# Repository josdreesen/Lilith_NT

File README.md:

# Lilith_NT

This database documents my attempt to recreate the 1980's ETH Lilith Modula-2 workstation. Both hardware and software is to be documented here.

The actual CPU will be identical to the original machine, shortcuts will be made to avoid some of the original problems :
- The disk was either a Honeywell-Bull 10Mb cartridge drive, or a 15Mb  MFM drive, controlled by a WD1001.
- NEW -> This is to be replaced by a DOM-disk with ATA interface.
- The original ha 4 PCB's with each 32 4116-type DRAM-chips, for a total of 128K 16bit words.
- NEW -> a single PCB will hold 16 256Kx4 chips, for a total of 1M 16bit words.
  Other characteristics will remain the same ( i.e. write access in 16bit words, read access in either 16bit of 64bit words)
- NEW : DIN41642 connectors will replace the original, hard to find and expensive 1.125" spaced board edge connectors.

Lilith-NT's hardware consists of 8 PCB's, all newly designed in a more compact format (Dual eurocard, 233.4mm x 152mm)

DPU : a MC6802 based debugging aid. This takes over the main busses in the system, allowing direct access to the hardware.
      Original schematic, slightly newer memory chips, new board layout.
      Not needed in normal operation of a Lilith.

ALU : the actual CPU, consisting of 4 AMD2901 bitslices, hardware stack and a 16bit barrel shifter.
      Original schematic with a new board layout.

MCU : microcode unit. Contains the microprogram that controls the bitslices, also has the microcode sequencer and clockgen circuitry.
      Original schematic with a new PCB layout, but now also has the memory address registers, originally in the CDP board.

IFU : instruction fetch unit. Also contains boot eprom. Original schematic with a new board layout.

DRAM: main memory, consisting of 16 4x256K DRAMs. Updated design of the original, using much denser chips. 
      Also contains the Dataregister which was originally in the CDP board.
      
DSP : Display unit / Videocard. Original schematic with a new board layout.      

IOP : IO board : new design, new PCB combining PS2 keyboard & mouse interface. 
      Also contains 2 serial channels, ATA/DOM disk, floppy interface and RTC chip.
      
Mainboard : carrries the above mentioned boards in dedicated slots.
            New design, using DIN-connectors instead of the PCB cardedge connectors to reduce cost and increase reliability.
            Goldplating PCB's is considerable more expensive than just using the DIN connectors.

The subdirectories, one for each pcb,  contain a .zip file with the gerbers, a .pdf with the schematic, a rendering of the PCB
and the Kicad Database itself.

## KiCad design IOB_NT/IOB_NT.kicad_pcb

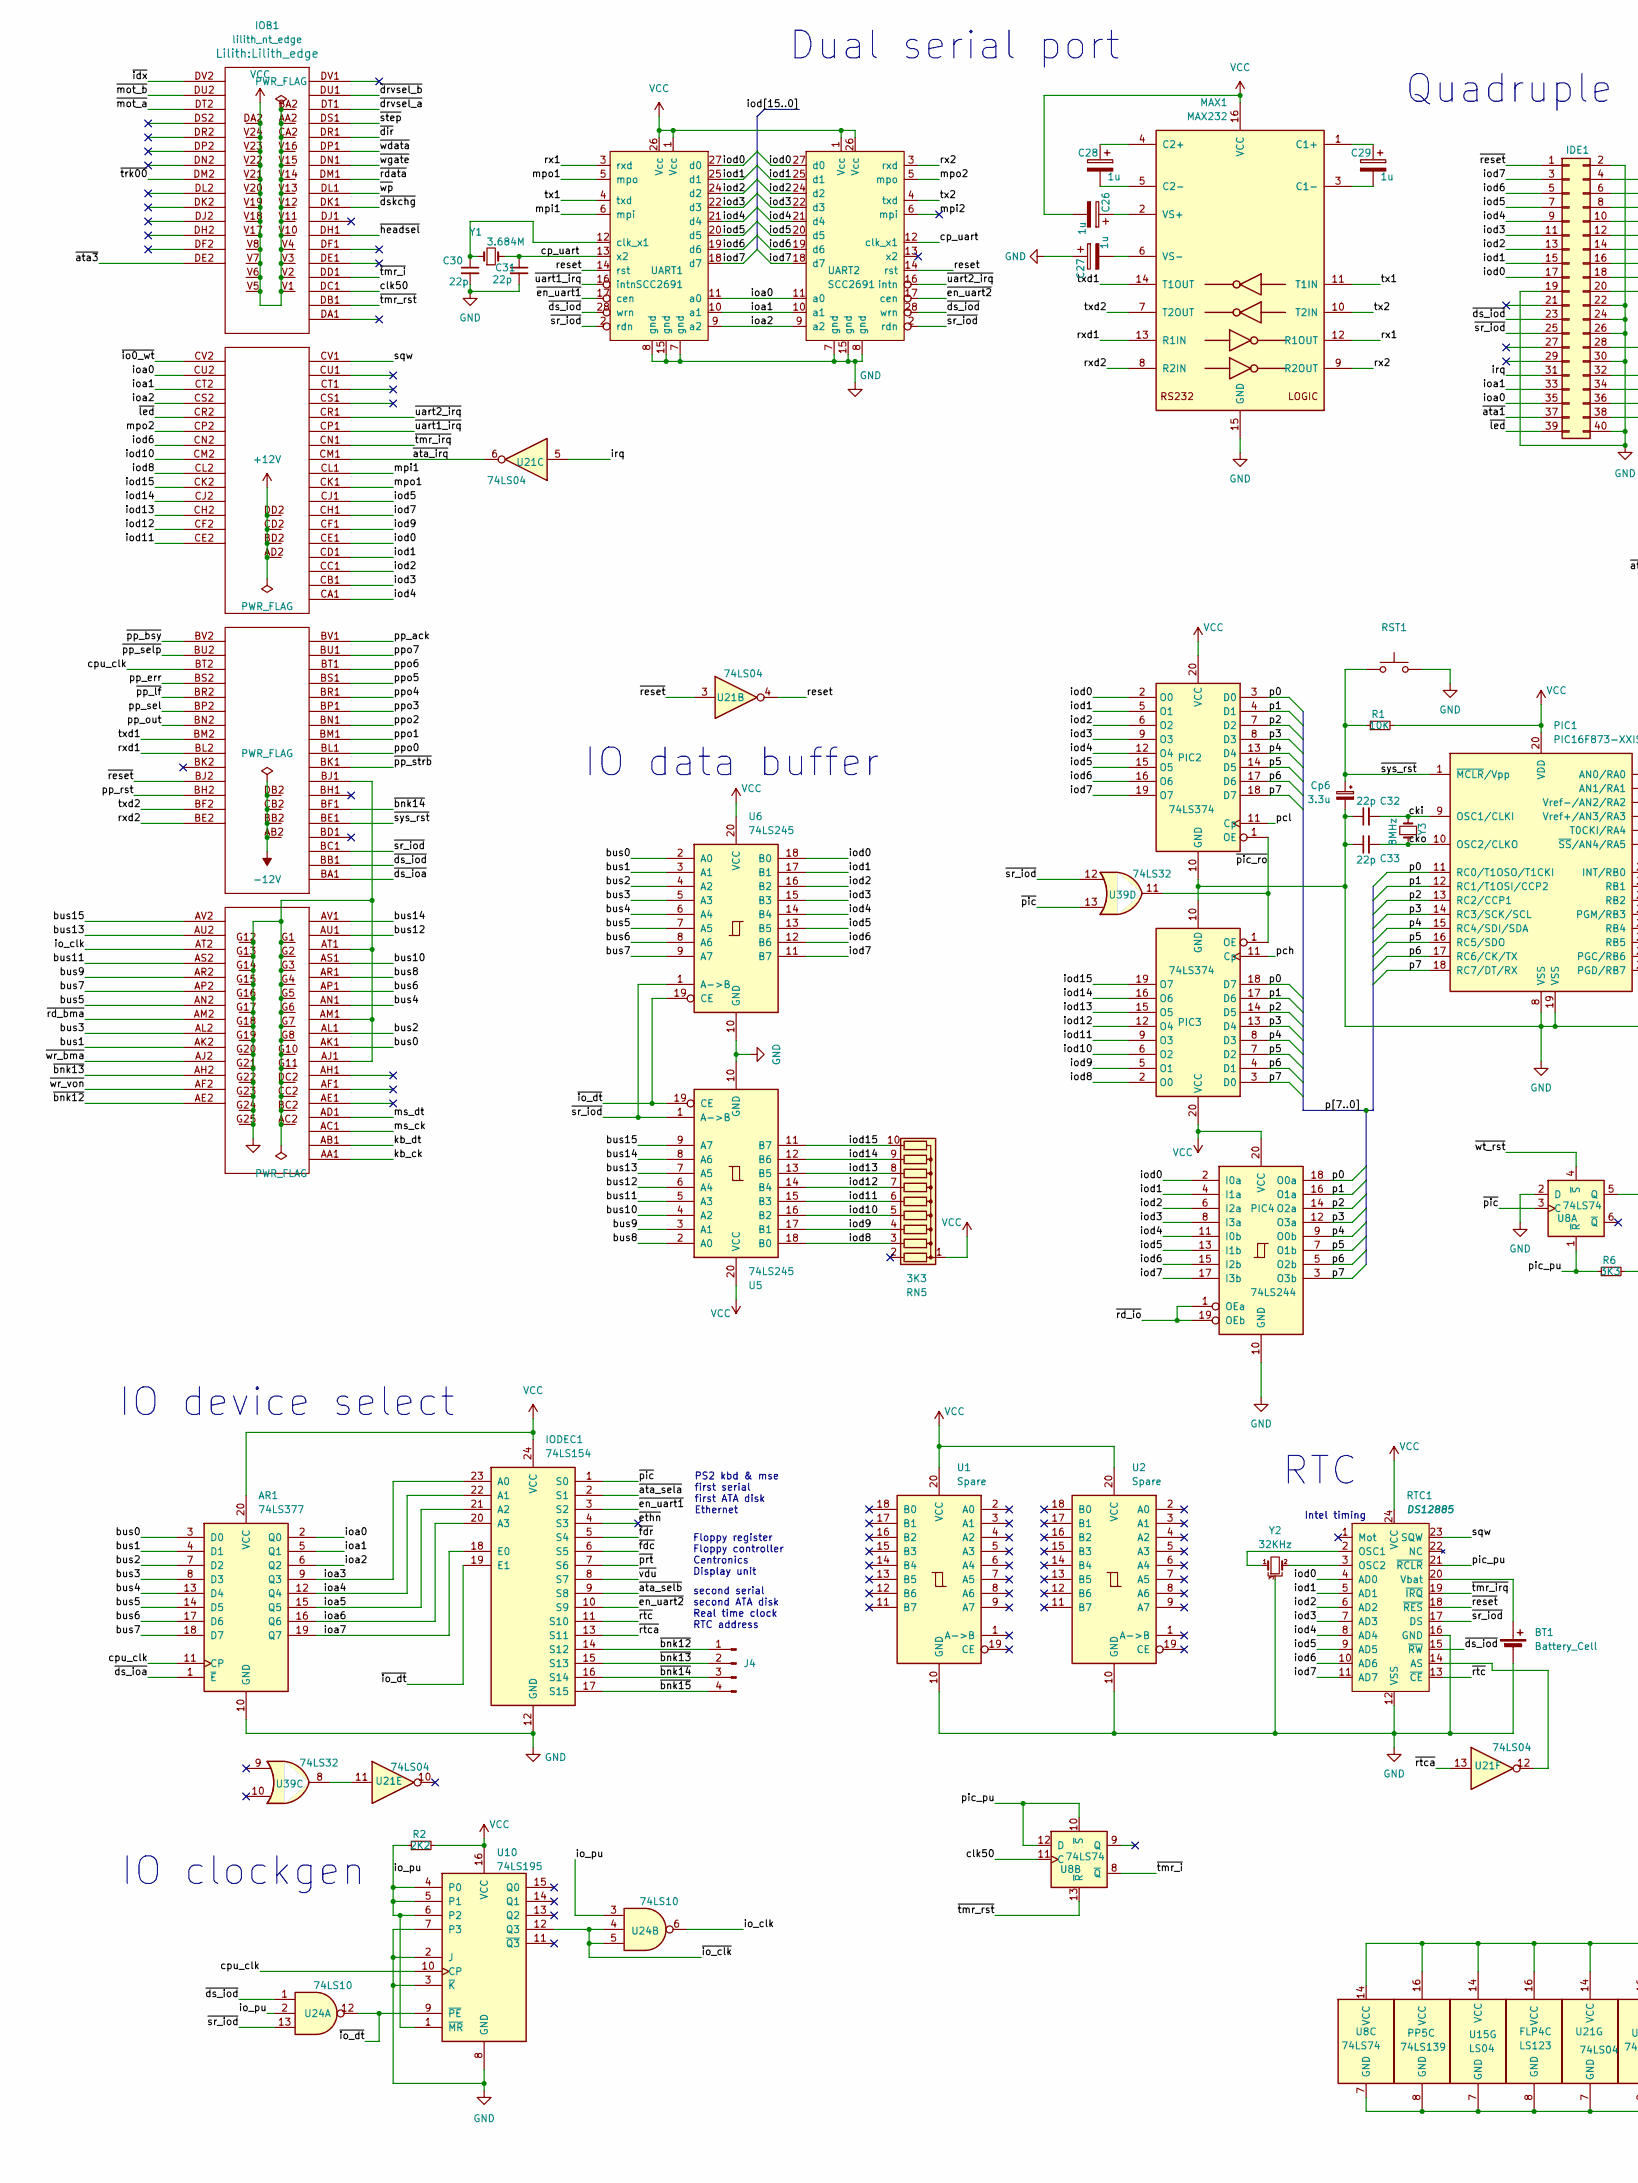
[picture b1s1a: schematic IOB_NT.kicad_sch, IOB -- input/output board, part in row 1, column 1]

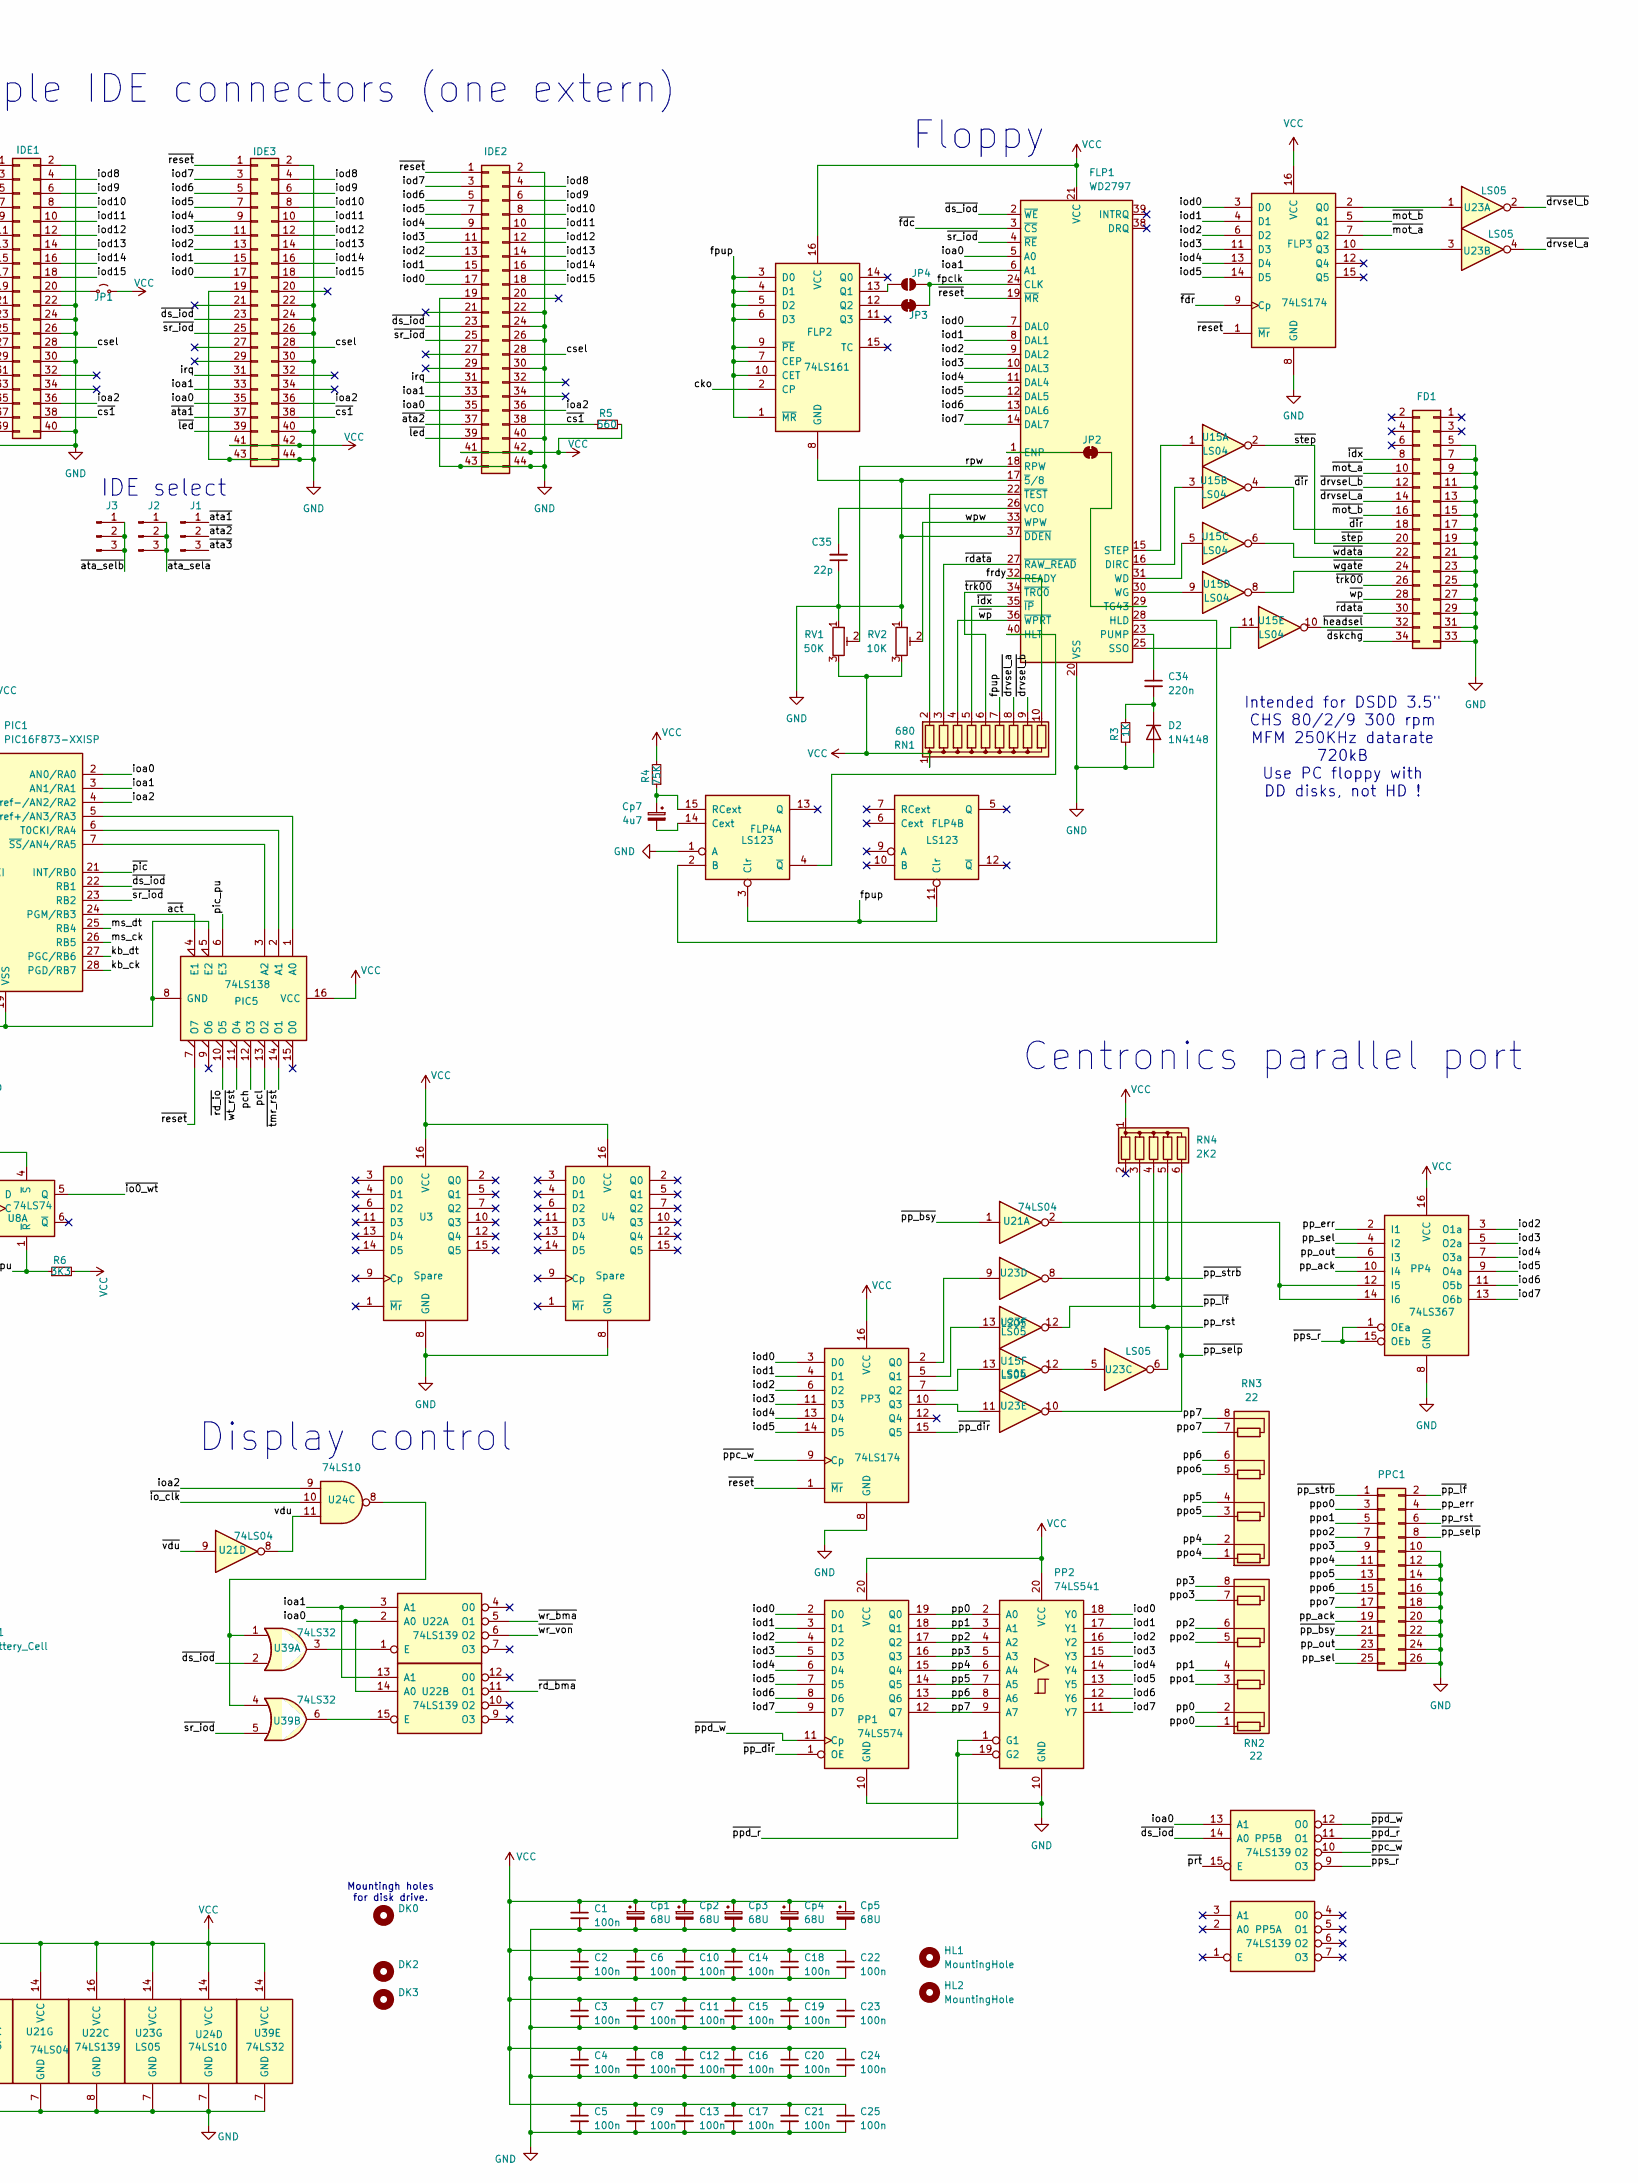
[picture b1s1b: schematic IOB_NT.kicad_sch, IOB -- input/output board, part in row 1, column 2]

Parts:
AR1: 74LS377; DIP-20_W7.62mm
BT1: Battery_Cell; BatteryHolder_MYOUNG_BS-07-A1BJ001_CR2032
C1, C2, C3, C4, C5, C6, C7, C8, C9, C10, C11, C12, C13, C14, C15, C16, C17, C18, C19, C20, C21, C22, C23, C24, C25: 100n; C_1206_3216Metric_Pad1.33x1.80mm_HandSolder
C26, C27, C28, C29: 1u; CP_Radial_Tantal_D4.5mm_P2.50mm
C30, C31: 22p; C_0805_2012Metric_Pad1.18x1.45mm_HandSolder
C32, C33: 22p; C_0805_2012Metric
C34: 220n; C_Rect_L7.0mm_W2.5mm_P5.00mm
C35: 22p; C_Disc_D3.0mm_W2.0mm_P2.50mm
Cp1, Cp2, Cp3, Cp4, Cp5: 68U; CP_PHP
Cp6: 3.3u; CP_Radial_D5.0mm_P2.50mm
Cp7: 4u7; CP_Radial_Tantal_D4.5mm_P2.50mm
D2: 1N4148; D_DO-35_SOD27_P7.62mm_Horizontal
DK0, DK2, DK3: MountingHole; MountingHole_2.7mm_M2.5
FD1: Conn_02x17_Odd_Even; IDC-Header_2x17_P2.54mm_Vertical
FLP1: WD2797; DIP-40_W15.24mm
FLP2: 74LS161; DIP-16_W7.62mm
FLP3: 74LS174; DIP-16_W7.62mm
FLP4: LS123; DIP-16_W7.62mm
HL1, HL2: MountingHole; Handle
IDE1: Conn_02x20_Odd_Even; IDC-Header_2x20_P2.54mm_Horizontal
IDE2, IDE3: Conn_02x22_Odd_Even; PinHeader_2x22_P2.00mm_Vertical
IOB1: lilith_nt_edge; Lilith_edge
IODEC1: 74LS154; DIP-24_W15.24mm
J1, J2, J3: Conn_01x03_Pin; PinHeader_1x03_P2.54mm_Vertical
J4: Conn_01x04_Pin; PinHeader_1x04_P2.54mm_Vertical
JP1: Jumper_2_Small_Open; PinHeader_1x02_P2.54mm_Vertical
JP2, JP3: SolderJumper_2_Bridged; SolderJumper-2_P1.3mm_Bridged_RoundedPad1.0x1.5mm
JP4: SolderJumper_2_Open; SolderJumper-2_P1.3mm_Open_RoundedPad1.0x1.5mm
MAX1: MAX232; DIP-16_W7.62mm
PIC1: PIC16F873-XXISP; DIP-28_W7.62mm_Socket
PIC2, PIC3: 74LS374; DIP-20_W7.62mm
PIC4: 74LS244; DIP-20_W7.62mm
PIC5: 74LS138; DIP-16_W7.62mm
PP1: 74LS574; DIP-20_W7.62mm
PP2: 74LS541; DIP-20_W7.62mm
PP3: 74LS174; DIP-16_W7.62mm
PP4: 74LS367; DIP-16_W7.62mm
PP5: 74LS139; DIP-16_W7.62mm
PPC1: Conn_02x13_Odd_Even; IDC-Header_2x13_P2.54mm_Vertical
R1: 10K; R_Axial_DIN0204_L3.6mm_D1.6mm_P7.62mm_Horizontal
R2: 2K2; R_Axial_DIN0204_L3.6mm_D1.6mm_P7.62mm_Horizontal
R3: 1K; R_Axial_DIN0204_L3.6mm_D1.6mm_P7.62mm_Horizontal
R4: 75K; R_Axial_DIN0204_L3.6mm_D1.6mm_P7.62mm_Horizontal
R5: 560; R_Axial_DIN0204_L3.6mm_D1.6mm_P7.62mm_Horizontal
R6: 3K3; R_Axial_DIN0204_L3.6mm_D1.6mm_P7.62mm_Horizontal
RN1: 680; R_Array_SIP10
RN2, RN3: 22; R_Array_SIP8
RN4: 2K2; R_Array_SIP6
RN5: 3K3; R_Array_SIP10
RST1: SW_Push; SW_PUSH_6mm
RTC1: DS12885; DIP-24_W15.24mm
RV1: 50K; Potentiometer_Bourns_3006P_Horizontal
RV2: 10K; Potentiometer_Bourns_3006P_Horizontal
U1, U2: Spare; DIP-20_W7.62mm
U3, U4: Spare; DIP-16_W7.62mm
U5, U6: 74LS245; DIP-20_W7.62mm
U8: 74LS74; DIP-14_W7.62mm
U10: 74LS195; DIP-16_W7.62mm
U15: LS04; DIP-14_W7.62mm
U21: 74LS04; DIP-14_W7.62mm
U22: 74LS139; DIP-16_W7.62mm
U23: LS05; DIP-14_W7.62mm
U24: 74LS10; DIP-14_W7.62mm
U39: 74LS32; DIP-14_W7.62mm
UART1, UART2: SCC2691; PLCC-28_THT-Socket
Y1: 3.684M; Crystal_HC49-U_Vertical
Y2: 32KHz; Crystal_AT310_D3.0mm_L10.0mm_Horizontal_1EP_style2
Y3: 8MHz; Crystal_HC52-6mm_Vertical

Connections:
+12V: IOB1.AD2, IOB1.BD2, IOB1.CD2, IOB1.DD2
-12V: IOB1.AB2, IOB1.BB2, IOB1.CB2, IOB1.DB2
/bus0: AR1.3 (D0), IOB1.AK1, U6.2 (A0)
/bus1: AR1.4 (D1), IOB1.AK2, U6.3 (A1)
/bus2: AR1.7 (D2), IOB1.AL1, U6.4 (A2)
/bus3: AR1.8 (D3), IOB1.AL2, U6.5 (A3)
/bus4: AR1.13 (D4), IOB1.AN1, U6.6 (A4)
/bus5: AR1.14 (D5), IOB1.AN2, U6.7 (A5)
/bus6: AR1.17 (D6), IOB1.AP1, U6.8 (A6)
/bus7: AR1.18 (D7), IOB1.AP2, U6.9 (A7)
/bus8: IOB1.AR1, U5.2 (A0)
/bus9: IOB1.AR2, U5.3 (A1)
/bus10: IOB1.AS1, U5.4 (A2)
/bus11: IOB1.AS2, U5.5 (A3)
/bus12: IOB1.AU1, U5.6 (A4)
/bus13: IOB1.AU2, U5.7 (A5)
/bus14: IOB1.AV1, U5.8 (A6)
/bus15: IOB1.AV2, U5.9 (A7)
/cki: C32.2, PIC1.9 (OSC1/CLKI), Y3.2
/cko: C33.2, FLP2.2 (CP), PIC1.10 (OSC2/CLKO), Y3.1
/clk50: IOB1.DC1, U8.11 (C)
/cp_uart: C31.1, UART1.13 (x2), UART2.12 (clk_x1), Y1.2
/cpu_clk: AR1.11 (CP), IOB1.BT2, U10.10 (CP)
/csel: IDE1.28, IDE2.28, IDE3.28
/fpclk: FLP1.24 (CLK), JP3.2 (B), JP4.2 (B)
/fpup: FLP2.1 (~MR), FLP2.3 (D0), FLP2.4 (D1), FLP2.5 (D2), FLP2.6 (D3), FLP2.7 (CEP), FLP2.9 (~PE), FLP2.10 (CET), FLP4.3 (Clr), FLP4.11 (Clr), RN1.7 (R6)
/frdy: FLP1.32 (READY), RN1.10 (R9)
/io_clk: IOB1.AT2, U24.6
/io_pu: R2.1, U10.1 (~MR), U10.4 (P0), U10.5 (P1), U10.6 (P2), U24.2, U24.3
/ioa0: AR1.2 (Q0), FLP1.5 (A0), IDE1.35, IDE2.35, IDE3.35, IOB1.CU2, PIC1.2 (AN0/RA0), PP5.13 (A1), U22.2 (A0), U22.14 (A0), UART1.11 (a0), UART2.11 (a0)
/ioa1: AR1.5 (Q1), FLP1.6 (A1), IDE1.33, IDE2.33, IDE3.33, IOB1.CT2, PIC1.3 (AN1/RA1), U22.3 (A1), U22.13 (A1), UART1.10 (a1), UART2.10 (a1)
/ioa2: AR1.6 (Q2), IDE1.36, IDE2.36, IDE3.36, IOB1.CS2, PIC1.4 (Vref-/AN2/RA2), U24.9, UART1.9 (a2), UART2.9 (a2)
/ioa3: AR1.9 (Q3), IODEC1.23 (A0)
/ioa4: AR1.12 (Q4), IODEC1.22 (A1)
/ioa5: AR1.15 (Q5), IODEC1.21 (A2)
/ioa6: AR1.16 (Q6), IODEC1.20 (A3)
/ioa7: AR1.19 (Q7), IODEC1.18 (E0)
/iod0: FLP1.7 (DAL0), FLP3.3 (D0), IDE1.17, IDE2.17, IDE3.17, IOB1.CE1, PIC2.2 (O0), PIC4.2 (I0a), PP1.2 (D0), PP2.18 (Y0), PP3.3 (D0), RTC1.4 (AD0), U6.18 (B0), UART1.27 (d0), UART2.27 (d0)
/iod1: FLP1.8 (DAL1), FLP3.4 (D1), IDE1.15, IDE2.15, IDE3.15, IOB1.CD1, PIC2.5 (O1), PIC4.4 (I1a), PP1.3 (D1), PP2.17 (Y1), PP3.4 (D1), RTC1.5 (AD1), U6.17 (B1), UART1.25 (d1), UART2.25 (d1)
/iod2: FLP1.9 (DAL2), FLP3.6 (D2), IDE1.13, IDE2.13, IDE3.13, IOB1.CC1, PIC2.6 (O2), PIC4.6 (I2a), PP1.4 (D2), PP2.16 (Y2), PP3.6 (D2), PP4.3 (O1a), RTC1.6 (AD2), U6.16 (B2), UART1.24 (d2), UART2.24 (d2)
/iod3: FLP1.10 (DAL3), FLP3.11 (D3), IDE1.11, IDE2.11, IDE3.11, IOB1.CB1, PIC2.9 (O3), PIC4.8 (I3a), PP1.5 (D3), PP2.15 (Y3), PP3.11 (D3), PP4.5 (O2a), RTC1.7 (AD3), U6.15 (B3), UART1.22 (d3), UART2.22 (d3)
/iod4: FLP1.11 (DAL4), FLP3.13 (D4), IDE1.9, IDE2.9, IDE3.9, IOB1.CA1, PIC2.12 (O4), PIC4.11 (I0b), PP1.6 (D4), PP2.14 (Y4), PP3.13 (D4), PP4.7 (O3a), RTC1.8 (AD4), U6.14 (B4), UART1.21 (d4), UART2.21 (d4)
/iod5: FLP1.12 (DAL5), FLP3.14 (D5), IDE1.7, IDE2.7, IDE3.7, IOB1.CJ1, PIC2.15 (O5), PIC4.13 (I1b), PP1.7 (D5), PP2.13 (Y5), PP3.14 (D5), PP4.9 (O4a), RTC1.9 (AD5), U6.13 (B5), UART1.20 (d5), UART2.20 (d5)
/iod6: FLP1.13 (DAL6), IDE1.5, IDE2.5, IDE3.5, IOB1.CN2, PIC2.16 (O6), PIC4.15 (I2b), PP1.8 (D6), PP2.12 (Y6), PP4.11 (O5b), RTC1.10 (AD6), U6.12 (B6), UART1.19 (d6), UART2.19 (d6)
/iod7: FLP1.14 (DAL7), IDE1.3, IDE2.3, IDE3.3, IOB1.CH1, PIC2.19 (O7), PIC4.17 (I3b), PP1.9 (D7), PP2.11 (Y7), PP4.13 (O6b), RTC1.11 (AD7), U6.11 (B7), UART1.18 (d7), UART2.18 (d7)
/iod8: IDE1.4, IDE2.4, IDE3.4, IOB1.CL2, PIC3.2 (O0), RN5.3 (R2), U5.18 (B0)
/iod9: IDE1.6, IDE2.6, IDE3.6, IOB1.CF1, PIC3.5 (O1), RN5.4 (R3), U5.17 (B1)
/iod10: IDE1.8, IDE2.8, IDE3.8, IOB1.CM2, PIC3.6 (O2), RN5.5 (R4), U5.16 (B2)
/iod11: IDE1.10, IDE2.10, IDE3.10, IOB1.CE2, PIC3.9 (O3), RN5.6 (R5), U5.15 (B3)
/iod12: IDE1.12, IDE2.12, IDE3.12, IOB1.CF2, PIC3.12 (O4), RN5.7 (R6), U5.14 (B4)
/iod13: IDE1.14, IDE2.14, IDE3.14, IOB1.CH2, PIC3.15 (O5), RN5.8 (R7), U5.13 (B5)
/iod14: IDE1.16, IDE2.16, IDE3.16, IOB1.CJ2, PIC3.16 (O6), RN5.9 (R8), U5.12 (B6)
/iod15: IDE1.18, IDE2.18, IDE3.18, IOB1.CK2, PIC3.19 (O7), RN5.10 (R9), U5.11 (B7)
/irq: IDE1.31, IDE2.31, IDE3.31, U21.5
/kb_ck: IOB1.AA1, PIC1.28 (PGD/RB7)
/kb_dt: IOB1.AB1, PIC1.27 (PGC/RB6)
/mpi1: IOB1.CL1, UART1.6 (mpi)
/mpi2: UART2.6 (mpi)
/mpo1: IOB1.CK1, UART1.5 (mpo)
/mpo2: IOB1.CP2, UART2.5 (mpo)
/ms_ck: IOB1.AC1, PIC1.26 (RB5)
/ms_dt: IOB1.AD1, PIC1.25 (RB4)
/p0: PIC1.11 (RC0/T1OSO/T1CKI), PIC2.3 (D0), PIC3.18 (D7), PIC4.18 (O0a)
/p1: PIC1.12 (RC1/T1OSI/CCP2), PIC2.4 (D1), PIC3.17 (D6), PIC4.16 (O1a)
/p2: PIC1.13 (RC2/CCP1), PIC2.7 (D2), PIC3.14 (D5), PIC4.14 (O2a)
/p3: PIC1.14 (RC3/SCK/SCL), PIC2.8 (D3), PIC3.13 (D4), PIC4.12 (O3a)
/p4: PIC1.15 (RC4/SDI/SDA), PIC2.13 (D4), PIC3.8 (D3), PIC4.9 (O0b)
/p5: PIC1.16 (RC5/SDO), PIC2.14 (D5), PIC3.7 (D2), PIC4.7 (O1b)
/p6: PIC1.17 (RC6/CK/TX), PIC2.17 (D6), PIC3.4 (D1), PIC4.5 (O2b)
/p7: PIC1.18 (RC7/DT/RX), PIC2.18 (D7), PIC3.3 (D0), PIC4.3 (O3b)
/pch: PIC3.11 (Cp), PIC5.12 (O3)
/pcl: PIC2.11 (Cp), PIC5.13 (O2)
/pic_pu: PIC5.6 (E3), R6.1, RTC1.21 (~RCLR), U8.1 (~R), U8.10 (~S), U8.12 (D)
/pp0: PP1.19 (Q0), PP2.2 (A0), RN2.2 (R1.2)
/pp1: PP1.18 (Q1), PP2.3 (A1), RN2.4 (R2.2)
/pp2: PP1.17 (Q2), PP2.4 (A2), RN2.6 (R3.2)
/pp3: PP1.16 (Q3), PP2.5 (A3), RN2.8 (R4.2)
/pp4: PP1.15 (Q4), PP2.6 (A4), RN3.2 (R1.2)
/pp5: PP1.14 (Q5), PP2.7 (A5), RN3.4 (R2.2)
/pp6: PP1.13 (Q6), PP2.8 (A6), RN3.6 (R3.2)
/pp7: PP1.12 (Q7), PP2.9 (A7), RN3.8 (R4.2)
/pp_ack: IOB1.BV1, PP4.10 (I4), PPC1.19
/pp_err: IOB1.BS2, PP4.2 (I1), PPC1.4
/pp_out: IOB1.BN2, PP4.6 (I3), PPC1.23
/pp_rst: IOB1.BH2, PPC1.6, RN4.3 (R2), U23.6
/pp_sel: IOB1.BP2, PP4.4 (I2), PPC1.25
/ppo0: IOB1.BL1, PPC1.3, RN2.1 (R1.1)
/ppo1: IOB1.BM1, PPC1.5, RN2.3 (R2.1)
/ppo2: IOB1.BN1, PPC1.7, RN2.5 (R3.1)
/ppo3: IOB1.BP1, PPC1.9, RN2.7 (R4.1)
/ppo4: IOB1.BR1, PPC1.11, RN3.1 (R1.1)
/ppo5: IOB1.BS1, PPC1.13, RN3.3 (R2.1)
/ppo6: IOB1.BT1, PPC1.15, RN3.5 (R3.1)
/ppo7: IOB1.BU1, PPC1.17, RN3.7 (R4.1)
/reset: U21.4, UART1.14 (rst), UART2.14 (rst)
/rpw: FLP1.18 (RPW), RV1.2
/rx1: MAX1.12 (R1OUT), UART1.3 (rxd)
/rx2: MAX1.9 (R2OUT), UART2.3 (rxd)
/rxd1: IOB1.BL2, MAX1.13 (R1IN)
/rxd2: IOB1.BE2, MAX1.8 (R2IN)
/sqw: IOB1.CV1, RTC1.23 (SQW)
/tx1: MAX1.11 (T1IN), UART1.4 (txd)
/tx2: MAX1.10 (T2IN), UART2.4 (txd)
/txd1: IOB1.BM2, MAX1.14 (T1OUT)
/txd2: IOB1.BF2, MAX1.7 (T2OUT)
/vdu: U21.8, U24.11
/wpw: FLP1.33 (WPW), RV2.2
/~act: PIC1.24 (PGM/RB3), PIC5.4 (E1)
/~ata1: IDE1.37, IDE3.37, J1.1
/~ata2: IDE2.37, J1.2
/~ata3: IOB1.DE2, J1.3
/~ata_irq: IOB1.CM1, U21.6
/~ata_sela: IODEC1.2 (S1), J2.1, J2.2, J2.3
/~ata_selb: IODEC1.9 (S8), J3.1, J3.2, J3.3
/~bnk12: IOB1.AE2, IODEC1.14 (S12), J4.1
/~bnk13: IOB1.AH2, IODEC1.15 (S13), J4.2
/~bnk14: IOB1.BF1, IODEC1.16 (S14), J4.3
/~bnk15: IODEC1.17 (S15), J4.4
/~cs1: IDE1.38, IDE2.38, IDE3.38, R5.1
/~dir: FD1.18, IOB1.DR1, U15.4
/~drvsel_a: FD1.14, IOB1.DT1, RN1.8 (R7), U23.4
/~drvsel_b: FD1.12, IOB1.DU1, RN1.9 (R8), U23.2
/~ds_ioa: AR1.1 (~E), IOB1.BA1
/~ds_iod: FLP1.2 (~WE), IDE1.23, IDE2.23, IDE3.23, IOB1.BB1, PIC1.22 (RB1), PP5.14 (A0), RTC1.15 (~RW), U24.1, U39.2, UART1.28 (wrn), UART2.28 (wrn)
/~dskchg: FD1.34, IOB1.DK1
/~en_uart1: IODEC1.3 (S2), UART1.17 (cen)
/~en_uart2: IODEC1.10 (S9), UART2.17 (cen)
/~ethn: IODEC1.4 (S3)
/~fdc: FLP1.3 (~CS), IODEC1.6 (S5)
/~fdr: FLP3.9 (Cp), IODEC1.5 (S4)
/~headsel: FD1.32, IOB1.DH1, U15.10
/~idx: FD1.8, FLP1.35 (~IP), IOB1.DV2, RN1.5 (R4)
/~io0_wt: IOB1.CV2, U8.5 (Q)
/~io_clk: U10.12 (Q3), U24.4, U24.5, U24.10
/~io_dt: IODEC1.19 (E1), U5.19 (CE), U6.19 (CE), U10.9 (~PE), U24.12
/~led: IDE1.39, IDE2.39, IDE3.39, IOB1.CR2
/~mot_a: FD1.10, FLP3.7 (Q2), IOB1.DT2
/~mot_b: FD1.16, FLP3.5 (Q1), IOB1.DU2
/~pic_ro: PIC2.1 (OE), PIC3.1 (OE), U39.11
/~pic: IODEC1.1 (S0), PIC1.21 (INT/RB0), U8.3 (C), U39.13
/~pp_bsy: IOB1.BV2, PPC1.21, U21.1
/~pp_dir: PP1.1 (OE), PP3.15 (Q5)
/~pp_lf: IOB1.BR2, PPC1.2, RN4.4 (R3), U23.12
/~pp_selp: IOB1.BU2, PPC1.8, RN4.6 (R5), U23.10
/~pp_strb: IOB1.BK1, PPC1.1, RN4.5 (R4), U23.8
/~ppc_w: PP3.9 (Cp), PP5.10 (O2)
/~ppd_r: PP2.1 (G1), PP2.19 (G2), PP5.11 (O1)
/~ppd_w: PP1.11 (Cp), PP5.12 (O0)
/~pps_r: PP4.1 (OEa), PP4.15 (OEb), PP5.9 (O3)
/~prt: IODEC1.7 (S6), PP5.15 (E)
/~rd_bma: IOB1.AM2, U22.11 (O1)
/~rd_io: PIC4.1 (OEa), PIC4.19 (OEb), PIC5.10 (O5)
/~rdata: FD1.30, FLP1.27 (~RAW_READ), IOB1.DM1, RN1.3 (R2)
/~reset: FLP1.19 (~MR), FLP3.1 (~Mr), IDE1.1, IDE2.1, IDE3.1, IOB1.BJ2, PIC5.7 (O7), PP3.1 (~Mr), RTC1.18 (~RES), U21.3
/~rtca: IODEC1.13 (S11), U21.13
/~rtc: IODEC1.11 (S10), RTC1.13 (~CE)
/~sr_iod: FLP1.4 (~RE), IDE1.25, IDE2.25, IDE3.25, IOB1.BC1, PIC1.23 (RB2), RTC1.17 (DS), U5.1 (A->B), U6.1 (A->B), U24.13, U39.5, U39.12, UART1.2 (rdn), UART2.2 (rdn)
/~step: FD1.20, IOB1.DS1, U15.2
/~sys_rst: Cp6.1, IOB1.BE1, PIC1.1 (~MCLR/Vpp), R1.1, RST1.1
/~tmr_irq: IOB1.CN1, RTC1.19 (~IRQ)
/~tmr_i: IOB1.DD1, U8.8 (~Q)
/~tmr_rst: IOB1.DB1, PIC5.14 (O1), U8.13 (~R)
/~trk00: FD1.26, FLP1.34 (~TR00), IOB1.DM2, RN1.6 (R5)
/~uart1_irq: IOB1.CP1, UART1.16 (intn)
/~uart2_irq: IOB1.CR1, UART2.16 (intn)
/~vdu: IODEC1.8 (S7), U21.9
/~wdata: FD1.22, IOB1.DP1, U15.6
/~wgate: FD1.24, IOB1.DN1, U15.8
/~wp: FD1.28, FLP1.36 (~WPRT), IOB1.DL1, RN1.4 (R3)
/~wr_bma: IOB1.AJ2, U22.5 (O1)
/~wr_von: IOB1.AF2, U22.6 (O2)
/~wt_rst: PIC5.11 (O4), U8.4 (~S)
GND: AR1.10 (GND), BT1.2 (-), C1.2, C2.2, C3.2, C4.2, C5.2, C6.2, C7.2, C8.2, C9.2, C10.2, C11.2, C12.2, C13.2, C14.2, C15.2, C16.2, C17.2, C18.2, C19.2, C20.2, C21.2, C22.2, C23.2, C24.2, C25.2, C27.1, C30.2, C31.2, C32.1, C33.1, C35.1, Cp1.2, Cp2.2, Cp3.2, Cp4.2, Cp5.2, Cp6.2, D2.2 (A), FD1.5, FD1.7, FD1.9, FD1.11, FD1.13, FD1.15, FD1.17, FD1.19, FD1.21, FD1.23, FD1.25, FD1.27, FD1.29, FD1.31, FD1.33, FLP1.17 (~5/8), FLP1.20 (VSS), FLP1.37 (~DDEN), FLP2.8 (GND), FLP3.8 (GND), FLP4.1 (A), FLP4.8 (GND), IDE1.2, IDE1.19, IDE1.22, IDE1.24, IDE1.26, IDE1.30, IDE1.40, IDE2.2, IDE2.19, IDE2.22, IDE2.24, IDE2.26, IDE2.30, IDE2.40, IDE2.43, IDE2.44, IDE3.2, IDE3.19, IDE3.22, IDE3.24, IDE3.26, IDE3.30, IDE3.40, IDE3.43, IDE3.44, IOB1.AC2, IOB1.AJ1, IOB1.AM1, IOB1.AT1, IOB1.BC2, IOB1.BJ1, IOB1.CC2, IOB1.DC2, IOB1.G1 (GND), IOB1.G2 (GND), IOB1.G3 (GND), IOB1.G4 (GND), IOB1.G5 (GND), IOB1.G6 (GND), IOB1.G7 (GND), IOB1.G8 (GND), IOB1.G10, IOB1.G11, IOB1.G12, IOB1.G13, IOB1.G14, IOB1.G15, IOB1.G16, IOB1.G17, IOB1.G18, IOB1.G19, IOB1.G20, IOB1.G21, IOB1.G22, IOB1.G23, IOB1.G24, IOB1.G25, IODEC1.12 (GND), MAX1.15 (GND), PIC1.8 (VSS), PIC1.19 (VSS), PIC2.10 (GND), PIC3.10 (GND), PIC4.10 (GND), PIC5.5 (E2), PIC5.8 (GND), PP1.10 (GND), PP2.10 (GND), PP3.8 (GND), PP4.8 (GND), PP5.8 (GND), PPC1.10, PPC1.12, PPC1.14, PPC1.16, PPC1.18, PPC1.20, PPC1.22, PPC1.24, PPC1.26, R3.1, RST1.2, RTC1.12 (VSS), RTC1.16 (GND), RV1.1, RV2.1, U1.10 (GND), U2.10 (GND), U3.8 (GND), U4.8 (GND), U5.10 (GND), U6.10 (GND), U8.2 (D), U8.7 (GND), U10.2 (J), U10.3 (~K), U10.7 (P3), U10.8 (GND), U15.7 (GND), U21.7 (GND), U22.8 (GND), U23.7 (GND), U24.7 (GND), U39.7 (GND), UART1.7 (gnd), UART1.8 (gnd), UART1.15 (gnd), UART2.7 (gnd), UART2.8 (gnd), UART2.15 (gnd), Y2.3
unnamed: BT1.1 (+), RTC1.20 (Vbat)
unnamed: C34.2, D2.1 (K), R3.2
unnamed: FLP1.16 (DIRC), U15.3
unnamed: FLP1.1 (ENP), JP2.1 (A)
unnamed: FLP1.28 (HLD), FLP4.2 (B)
unnamed: FLP1.40 (HLT), FLP4.4 (~Q)
unnamed: C34.1, FLP1.23 (PUMP)
unnamed: FLP1.25 (SSO), U15.11
unnamed: FLP1.15 (STEP), U15.1
unnamed: FLP1.29 (TG43), JP2.2 (B)
unnamed: C35.2, FLP1.26 (VCO)
unnamed: FLP1.31 (WD), U15.5
unnamed: FLP1.30 (WG), U15.9
unnamed: FLP1.22 (~TEST), RN1.2 (R1)
unnamed: FLP2.13 (Q1), JP4.1 (A)
unnamed: FLP2.12 (Q2), JP3.1 (A)
unnamed: FLP3.2 (Q0), U23.1
unnamed: FLP3.10 (Q3), U23.3
unnamed: Cp7.2, FLP4.14 (Cext)
unnamed: Cp7.1, FLP4.15 (RCext), R4.1
unnamed: IDE1.20, JP1.1 (A)
unnamed: C29.1, MAX1.1 (C1+)
unnamed: C29.2, MAX1.3 (C1-)
unnamed: C28.1, MAX1.4 (C2+)
unnamed: C28.2, MAX1.5 (C2-)
unnamed: C26.1, MAX1.2 (VS+)
unnamed: C27.2, MAX1.6 (VS-)
unnamed: PIC1.6 (T0CKI/RA4), PIC5.2 (A1)
unnamed: PIC1.5 (Vref+/AN3/RA3), PIC5.1 (A0)
unnamed: PIC1.7 (~SS/AN4/RA5), PIC5.3 (A2)
unnamed: PP3.2 (Q0), U23.9
unnamed: PP3.5 (Q1), U23.13
unnamed: PP3.7 (Q2), U15.13
unnamed: PP3.10 (Q3), U23.11
unnamed: PP4.12 (I5), PP4.14 (I6), U21.2
unnamed: RTC1.14 (AS), U21.12
unnamed: RTC1.2 (OSC1), Y2.1
unnamed: RTC1.3 (OSC2), Y2.2
unnamed: U15.12, U23.5
unnamed: U21.11, U39.8
unnamed: U22.1 (E), U39.3
unnamed: U22.15 (E), U39.6
unnamed: U24.8, U39.1, U39.4
unnamed: C30.1, UART1.12 (clk_x1), Y1.1
VCC: AR1.20 (VCC), C1.1, C2.1, C3.1, C4.1, C5.1, C6.1, C7.1, C8.1, C9.1, C10.1, C11.1, C12.1, C13.1, C14.1, C15.1, C16.1, C17.1, C18.1, C19.1, C20.1, C21.1, C22.1, C23.1, C24.1, C25.1, C26.2, Cp1.1, Cp2.1, Cp3.1, Cp4.1, Cp5.1, FLP1.21 (VCC), FLP2.16 (VCC), FLP3.16 (VCC), FLP4.16 (VCC), IDE2.41, IDE2.42, IDE3.41, IDE3.42, IOB1.AA2, IOB1.BA2, IOB1.CA2, IOB1.DA2, IOB1.V1 (VCC), IOB1.V2 (VCC), IOB1.V3 (VCC), IOB1.V4 (VCC), IOB1.V5 (VCC), IOB1.V6 (VCC), IOB1.V7 (VCC), IOB1.V8 (VCC), IOB1.V10, IOB1.V11, IOB1.V12, IOB1.V13, IOB1.V14, IOB1.V15, IOB1.V16, IOB1.V17, IOB1.V18, IOB1.V19, IOB1.V20, IOB1.V21, IOB1.V22, IOB1.V23, IOB1.V24, IODEC1.24 (VCC), JP1.2 (B), MAX1.16 (VCC), PIC1.20 (VDD), PIC2.20 (VCC), PIC3.20 (VCC), PIC4.20 (VCC), PIC5.16 (VCC), PP1.20 (VCC), PP2.20 (VCC), PP3.16 (VCC), PP4.16 (VCC), PP5.16 (VCC), R1.2, R2.2, R4.2, R5.2, R6.2, RN1.1 (common), RN4.1 (common), RN5.1 (common), RTC1.24 (VCC), RV1.3, RV2.3, U1.20 (VCC), U2.20 (VCC), U3.16 (VCC), U4.16 (VCC), U5.20 (VCC), U6.20 (VCC), U8.14 (VCC), U10.16 (VCC), U15.14 (VCC), U21.14 (VCC), U22.16 (VCC), U23.14 (VCC), U24.14 (VCC), U39.14 (VCC), UART1.1 (Vcc), UART1.26 (Vcc), UART2.1 (Vcc), UART2.26 (Vcc)

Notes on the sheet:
Floppy
IO device select
Centronics parallel port
IDE select
PS2 kbd & mse first serial first ATA disk Ethernet
Intended for DSDD 3.5" CHS 80/2/9 300 rpm MFM 250KHz datarate 720kB Use PC floppy with DD disks, not HD !
Dual serial port
Intel timing
RTC
IO data buffer
IO clockgen
Floppy register Floppy controller Centronics Display unit
Mountingh holes for disk drive.
Quadruple IDE connectors (one extern)
second serial second ATA disk Real time clock RTC address
Display control

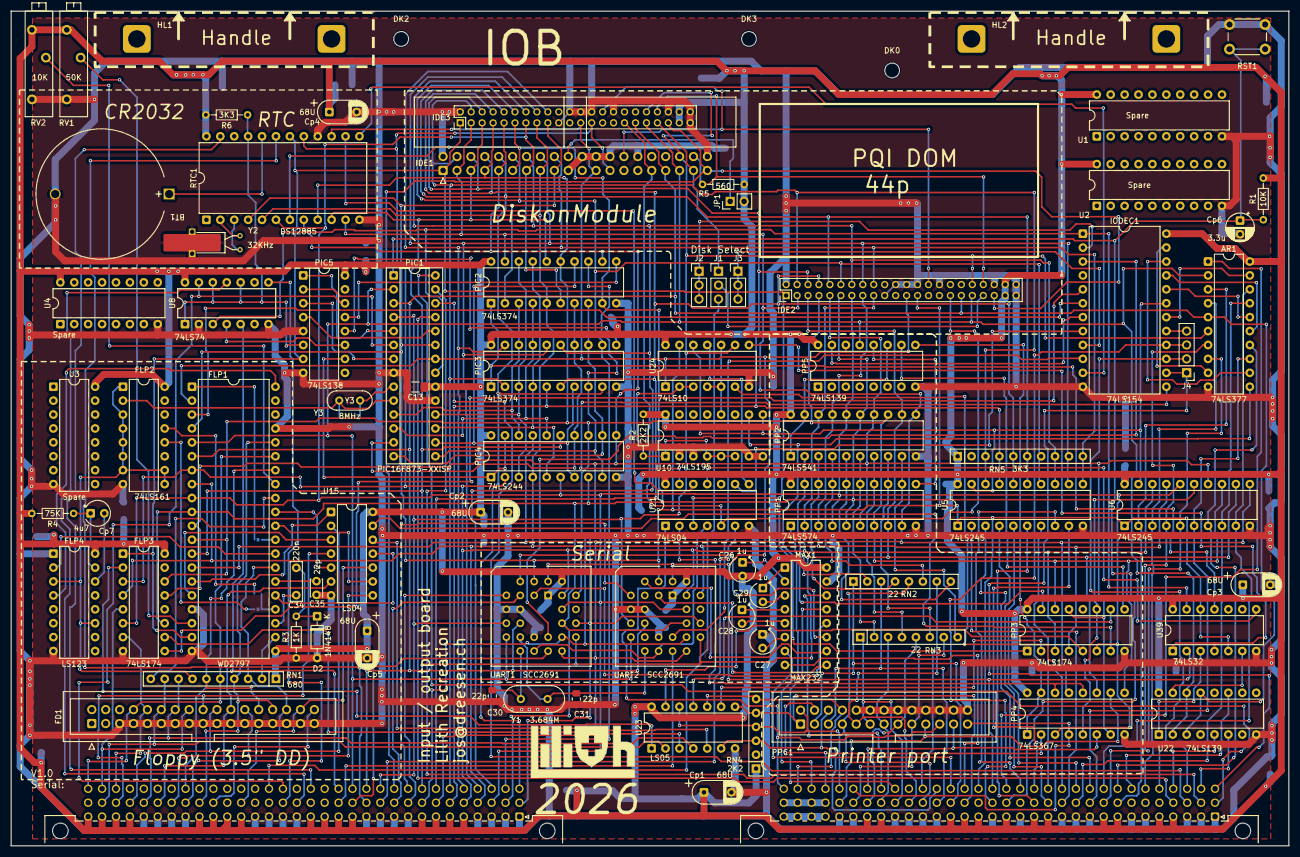
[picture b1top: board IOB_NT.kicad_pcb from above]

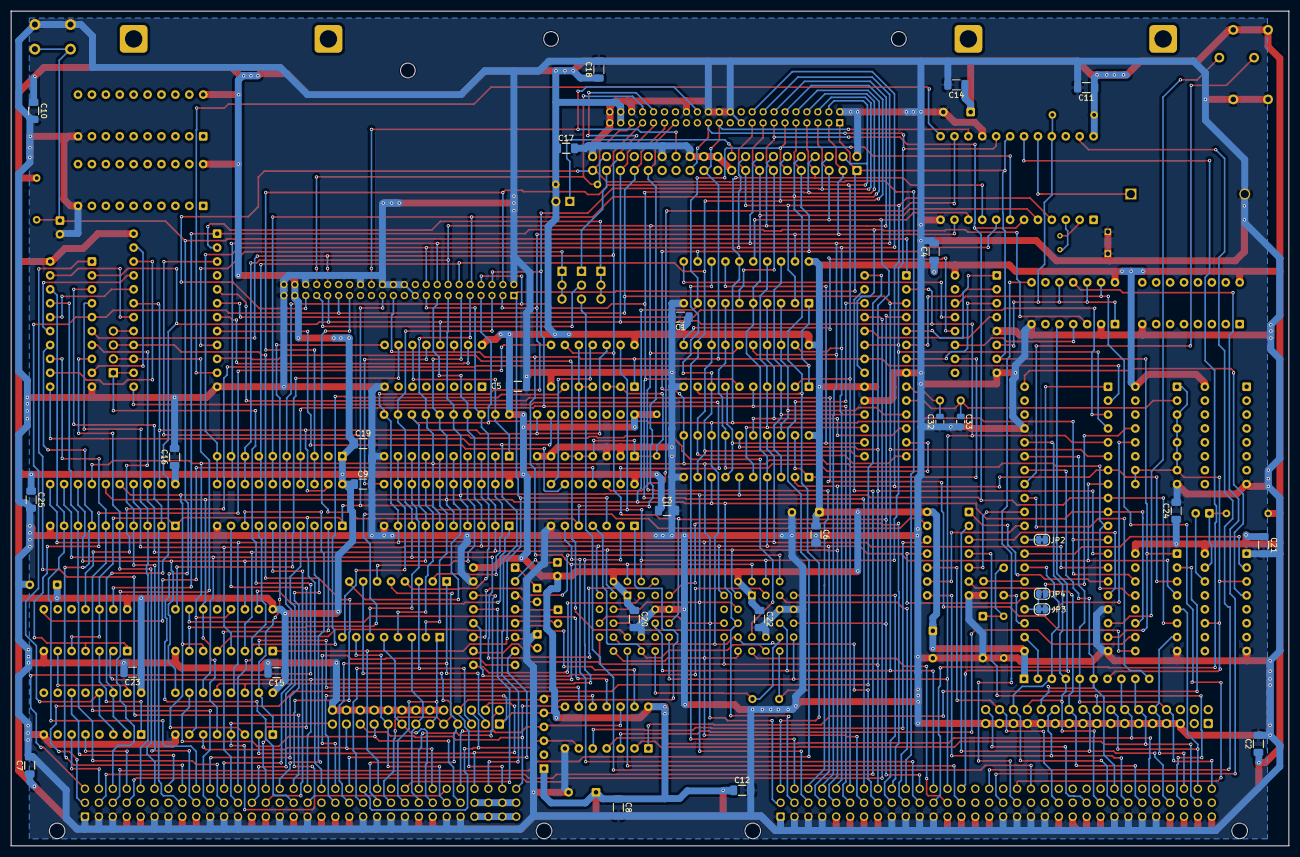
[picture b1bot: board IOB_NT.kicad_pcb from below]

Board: 2 copper layers, 233.3 x 152.4 mm, 114 parts (29 on the bottom side), 216 nets.
